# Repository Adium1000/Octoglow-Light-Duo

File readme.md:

Octoglow Light Duo is an LED strip controller capable of controlling two LED strips at the same time, receiving IR signals from a remote control designed for specific controllers as well as from custom IR commands, supporting power from an external source if the power supply of the microcontroller used is too weak, and also featuring a buzzer for audible feedback

So maybe you’ve come across some cheap LED controllers that use MOSFETs, have a Bluetooth app full of ads, are unstable, and break at the slightest jolt The idea behind my project is to create a reliable version that can control two sets of LEDs, has a buzzer, an IR sensor, and dedicated software that syncs with music, notifications, and other telemetry data that a user can provide all without any ads or sketchy software, running securely on your local network.

1. Open Octoglow.ino in the Arduino IDE (You can get it form /Firmware/)
2. Install the ESP32 board package from Boards Manager, if you don't have it yet.
3. Install the required libraries from the Library Manager: `Arduino.h`
4. Select your board and the correct serial port.
5. Upload the firmware.

It requires an ESP32 C3/S3 MINI board + Octoglow firmware to function as intended.

| Component | Quantity | Unit Price (USD) | Total Price (USD) |
|:--|--:|--:|--:|
| [100 nF 50 V X7R capacitor, 0603 (C1; JLCPCB C14663)](https://jlcpcb.com/partdetail/C14663) | 5 | $0.010800 | $0.0540 |
| [AO3400A N-channel MOSFET, SOT-23 (Q1–Q6; JLCPCB C20917)](https://jlcpcb.com/partdetail/AO3400A/C20917) | 30 | $0.097100 | $2.9130 |
| [220 Ω ±1% resistor, 0603 (R1/R3/R5/R7/R9/R11; JLCPCB C22962)](https://jlcpcb.com/partdetail/0603WAF2200T5E/C22962) | 30 | $0.003300 | $0.0990 |
| [10 kΩ ±1% resistor, 0603 (R2/R4/R6/R8/R10/R12; JLCPCB C25804)](https://jlcpcb.com/partdetail/0603WAF1002T5E/C25804) | 30 | $0.002400 | $0.0720 |
| [1 kΩ ±1% resistor, 0603 (R13; JLCPCB C21190)](https://jlcpcb.com/partdetail/0603WAF1001T5E/C21190) | 5 | $0.003000 | $0.0150 |
| [KF301-2P 2-pin screw terminal block, 5 mm](https://sigmanortec.ro/Conector-PCB-2-pini-KF301-2P-5mm-p136284289) | 5 | $0.259330 | $1.2966 |
| [ESP32-C3 SuperMini development board](https://sigmanortec.ro/placa-dezvoltare-esp32-c3-supermini-33v-wifi-bluetooth) | 1 | $5.625132 | $5.6251 |
| [Passive 5 V buzzer](https://sigmanortec.ro/Buzzer-pasiv-5v-p172425809) | 1 | $0.305714 | $0.3057 |
| [PCB fabrication](https://jlcpcb.com/) | 1 | $14.067000 | $14.0670 |
| [Sigmanortec shipping (14.95 RON)](https://sigmanortec.ro/) | 1 | $3.152013 | $3.1520 |
| [JLCPCB shipping](https://jlcpcb.com/) | 1 | $16.110000 | $16.1100 |
| **GRAND TOTAL** | | | **$43.7095** |

- The firmware was never being tested
- I need to release a case for this controller after havig it
- Integrate the firmware with octoglow connect

AI contributed to this project in the following ways:
- Helped me choose efficient components for my schematics
- Helped me learn how to use a MOSFET
- Performed schematic, PCB, and DRM checks
- Was involved in firmware development

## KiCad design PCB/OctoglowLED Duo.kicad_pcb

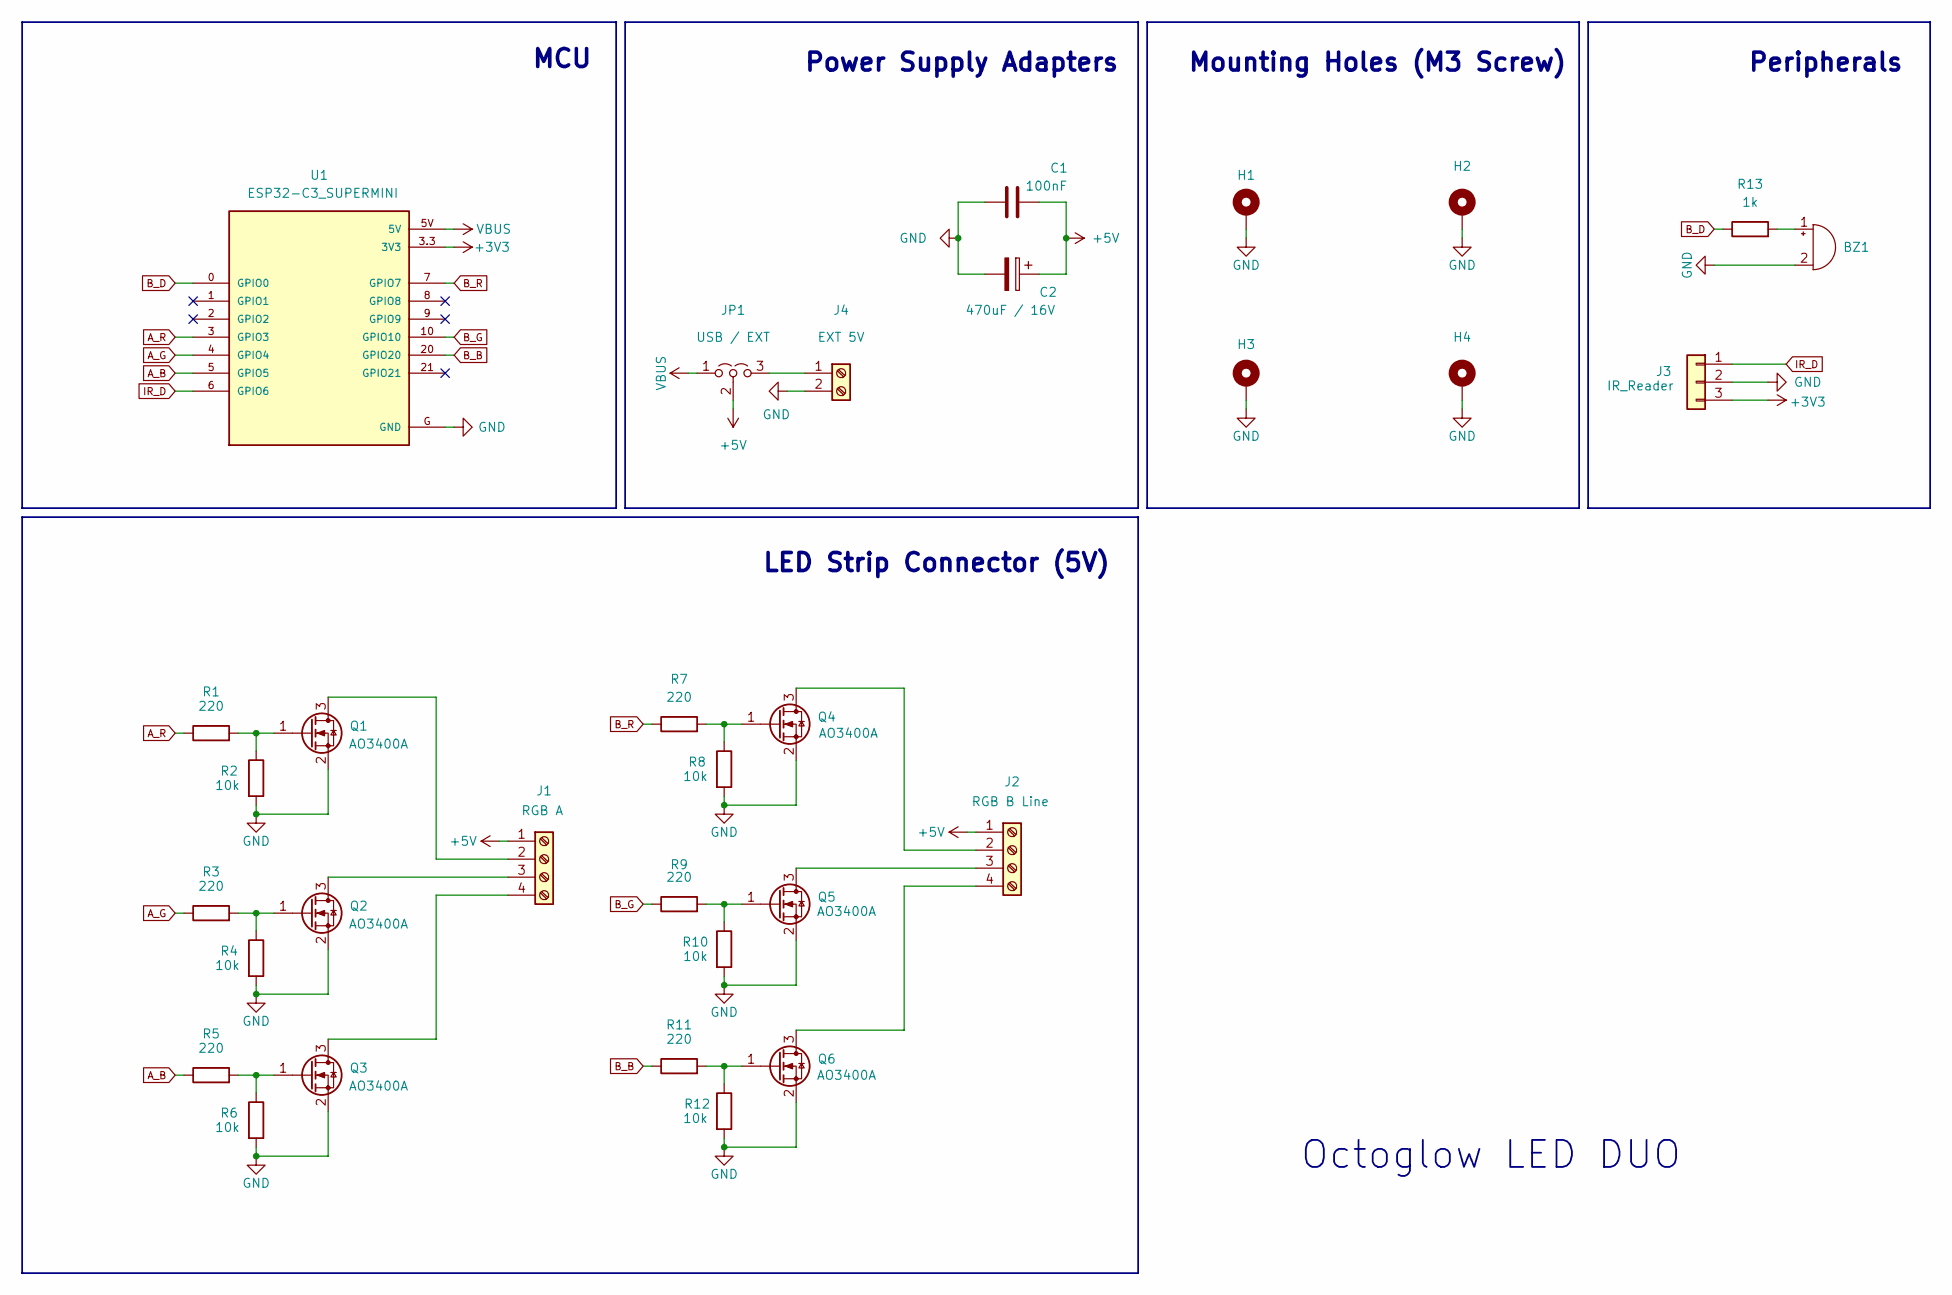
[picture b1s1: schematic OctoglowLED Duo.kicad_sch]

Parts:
BZ1: Buzzer; Buzzer_TDK_PS1240P02BT_D12.2mm_H6.5mm; MPN PS1240P02BT
C1: 100nF; C_0603_1608Metric; LCSC C14663
C2: 470uF / 16V; CP_Radial_D8.0mm_P3.50mm; LCSC C165573
H1, H2, H3, H4: M3; MountingHole_3.2mm_M3_Pad
J1: RGB A; TerminalBlock_Phoenix_MKDS-1,5-4-5.08_1x04_P5.08mm_Horizont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; LCSC C5443561
J2: RGB B Line; TerminalBlock_Phoenix_MKDS-1,5-4-5.08_1x04_P5.08mm_Horizont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; LCSC C5443561
J3: IR_Reader; PinHeader_1x03_P2.54mm_Vertical
J4: EXT 5V; TerminalBlock_Phoenix_MKDS-1,5-2-5.08_1x02_P5.08mm_Horizont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; MPN MKDS 1,5/2-5,08
JP1: USB / EXT; PinHeader_1x03_P2.54mm_Vertical; MPN TSW-103-07-G-S
Q1, Q2, Q3, Q4, Q5, Q6: AO3400A; SOT-23
R1, R3, R5, R7, R9, R11: 220; R_0603_1608Metric; Tolerance 1%; LCSC C22962
R2, R4, R6, R8, R10, R12: 10k; R_0603_1608Metric; Tolerance 1%; LCSC C25804
R13: 1k; R_0603_1608Metric; Tolerance 1%; LCSC C21190
U1: ESP32-C3_SUPERMINI; ESP32_C3_SuperMini_Socket

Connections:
+3V3: J3.3, U1.3.3 (3V3)
+5V: C1.1, C2.1, J1.1, J2.1, JP1.2 (C)
A_B: R5.1, U1.5 (GPIO5)
A_G: R3.1, U1.4 (GPIO4)
A_R: R1.1, U1.3 (GPIO3)
B_B: R11.1, U1.20 (GPIO20)
B_D: R13.1, U1.0 (GPIO0)
B_G: R9.1, U1.10 (GPIO10)
B_R: R7.1, U1.7 (GPIO7)
GND: BZ1.2 (-), C1.2, C2.2, H1.1, H2.1, H3.1, H4.1, J3.2, J4.2, Q1.2 (S), Q2.2 (S), Q3.2 (S), Q4.2 (S), Q5.2 (S), Q6.2 (S), R2.2, R4.2, R6.2, R8.2, R10.2, R12.2, U1.G (GND)
IR_D: J3.1, U1.6 (GPIO6)
unnamed: BZ1.1 (+), R13.2
unnamed: J1.2, Q1.3 (D)
unnamed: J1.3, Q2.3 (D)
unnamed: J1.4, Q3.3 (D)
unnamed: J2.2, Q4.3 (D)
unnamed: J2.3, Q5.3 (D)
unnamed: J2.4, Q6.3 (D)
unnamed: J4.1, JP1.3 (B)
unnamed: Q1.1 (G), R1.2, R2.1
unnamed: Q2.1 (G), R3.2, R4.1
unnamed: Q3.1 (G), R5.2, R6.1
unnamed: Q4.1 (G), R7.2, R8.1
unnamed: Q5.1 (G), R9.2, R10.1
unnamed: Q6.1 (G), R11.2, R12.1
VBUS: JP1.1 (A), U1.5V

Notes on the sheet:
Peripherals
Octoglow LED DUO
Power Supply Adapters
Mounting Holes (M3 Screw)
MCU
LED Strip Connector (5V)

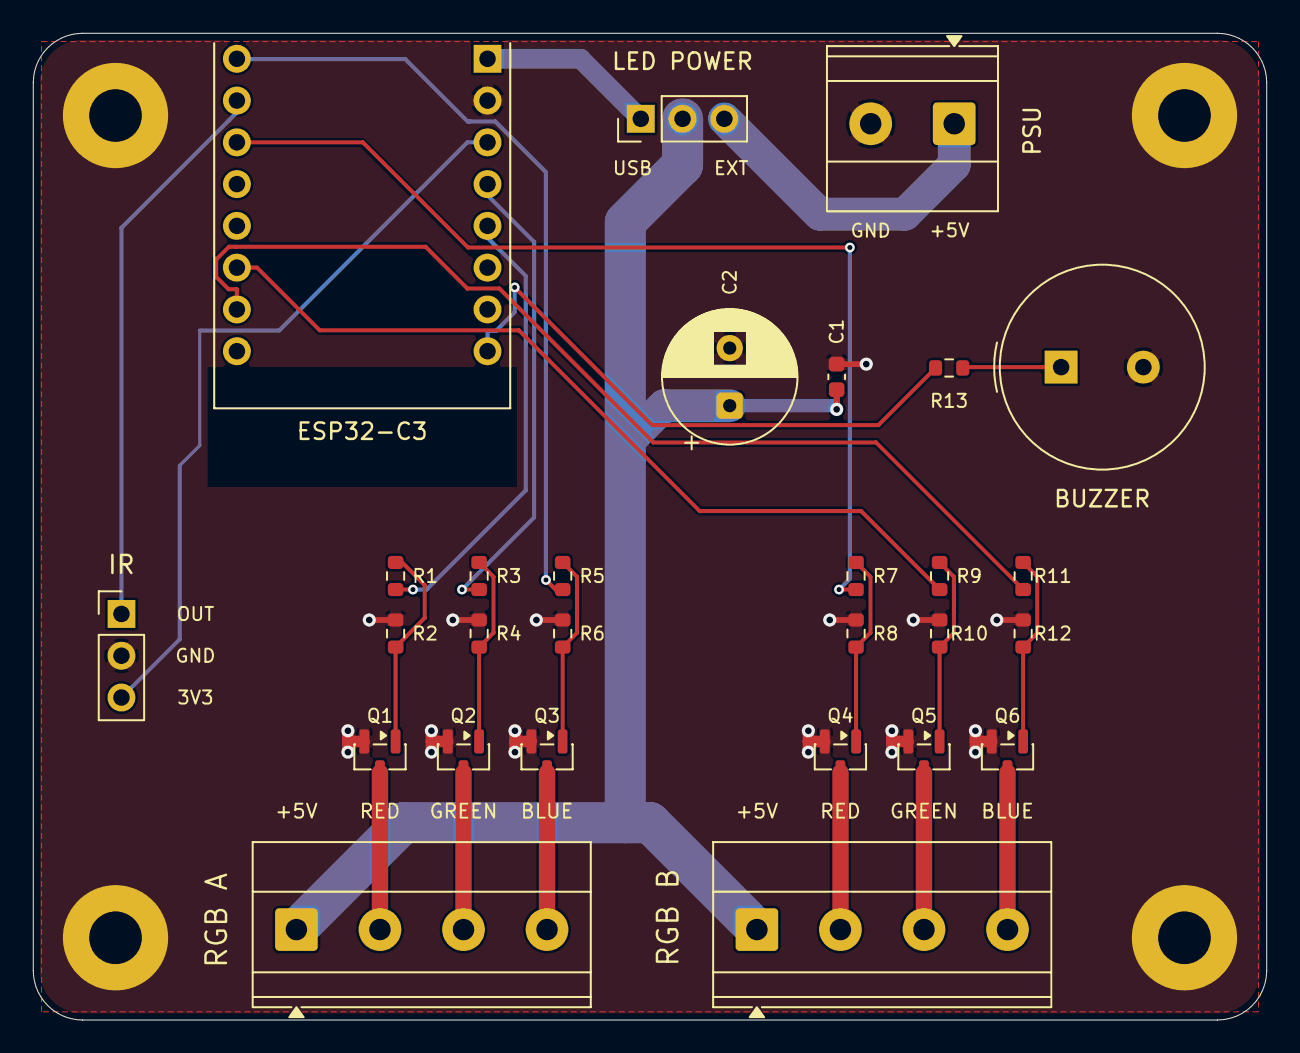
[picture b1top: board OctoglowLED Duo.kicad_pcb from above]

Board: 2 copper layers, 75.0 x 60.0 mm, 32 parts (0 on the bottom side), 26 nets.

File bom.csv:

Component,Quantity,Unit Price (USD),Total Price (USD)
"100 nF 50 V X7R capacitor, 0603 (C1; JLCPCB C14663) ",5,$0.010800,$0.0540
"AO3400A N-channel MOSFET, SOT-23 (Q1–Q6; JLCPCB C20917)",30,$0.097100,$2.9130
"220 Ω ±1% resistor, 0603 (R1/R3/R5/R7/R9/R11; JLCPCB C22962) ",30,$0.003300,$0.0990
"10 kΩ ±1% resistor, 0603 (R2/R4/R6/R8/R10/R12; JLCPCB C25804) ",30,$0.002400,$0.0720
"1 kΩ ±1% resistor, 0603 (R13; JLCPCB C21190) ",5,$0.003000,$0.0150
"KF301-2P 2-pin screw terminal block, 5 mm ",5,$0.259330,$1.2966
ESP32-C3 SuperMini development board ,1,$5.625132,$5.6251
Passive 5 V buzzer ,1,$0.305714,$0.3057
"PCB fabrication ",1,$14.067000,$14.0670
Sigmanortec shipping (14.95 RON) ,1,$3.152013,$3.1520
JLCPCB shipping ,1,$16.110000,$16.1100
GRAND TOTAL,,,$43.7095
